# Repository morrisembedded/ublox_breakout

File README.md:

# ublox_breakout
EAGLE CAD files - Created in EAGLE 7.7.0

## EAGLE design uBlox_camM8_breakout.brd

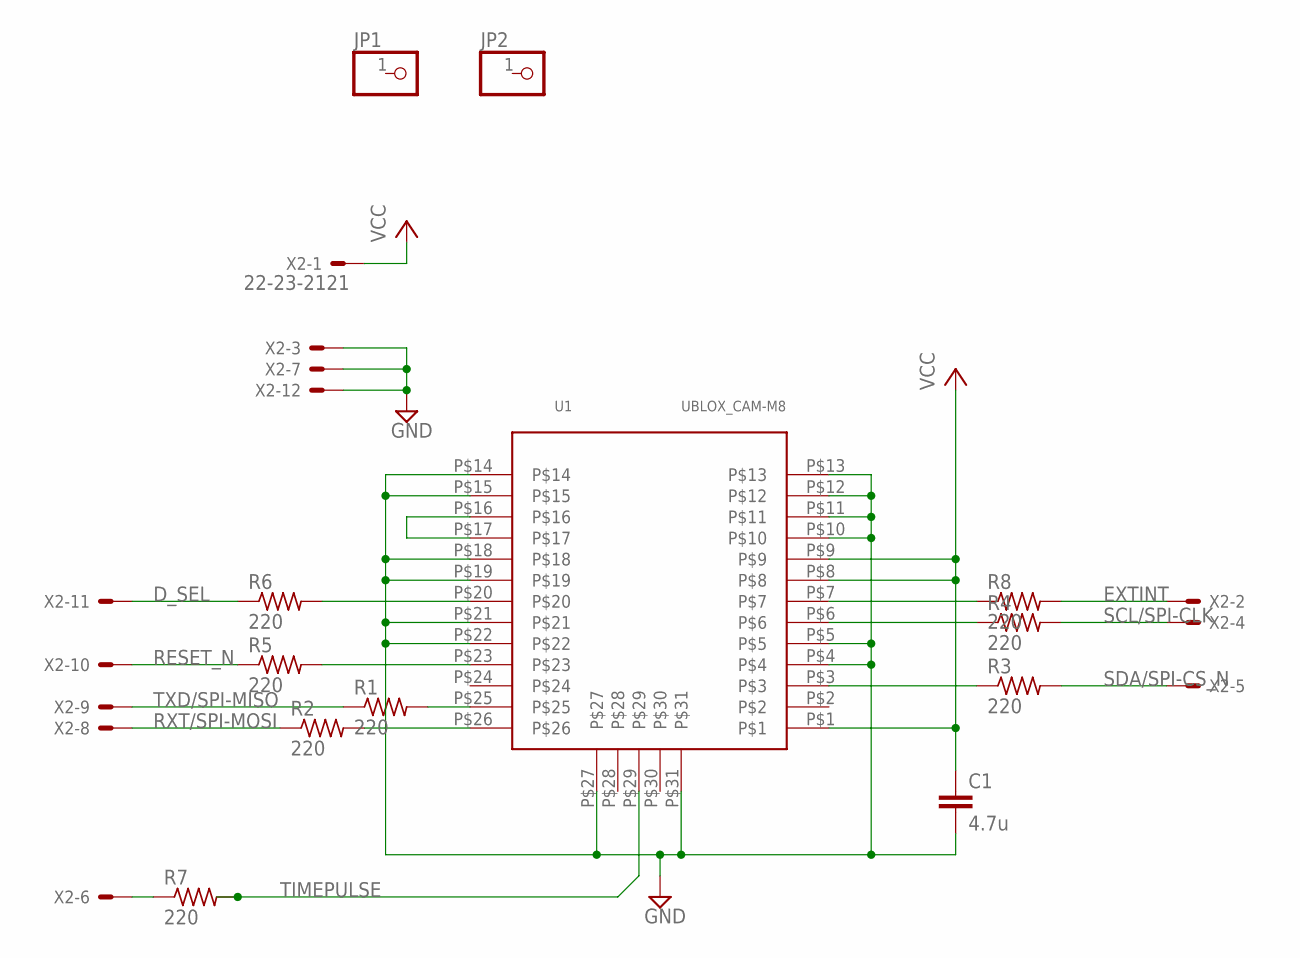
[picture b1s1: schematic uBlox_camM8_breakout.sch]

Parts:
C1: 4.7u; C0805
JP1, JP2: PINHD-1X1; 1X01
R1, R2, R3, R4, R5, R6, R7, R8: 220; R0402
U1: UBLOX_CAM-M8
X2: 22-23-2121

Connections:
D_SEL: R6.1, X2.11
EXTINT: R8.2, X2.2
GND: C1.2, U1.P$4, U1.P$5, U1.P$10, U1.P$11, U1.P$12, U1.P$13, U1.P$14, U1.P$15, U1.P$18, U1.P$19, U1.P$21, U1.P$22, U1.P$27, U1.P$31, X2.3, X2.7, X2.12
unnamed: R1.2, U1.P$25
unnamed: R2.2, U1.P$26
unnamed: U1.P$16, U1.P$17
unnamed: R3.1, U1.P$3
unnamed: R4.1, U1.P$6
unnamed: R8.1, U1.P$7
unnamed: R5.2, U1.P$23
unnamed: R6.2, U1.P$20
unnamed: R7.1, X2.6
RESET_N: R5.1, X2.10
RXT/SPI-MOSI: R2.1, X2.8
SCL/SPI-CLK: R4.2, X2.4
SDA/SPI-CS_N: R3.2, X2.5
TIMEPULSE: R7.2, U1.P$29
TXD/SPI-MISO: R1.1, X2.9
VCC: C1.1, U1.P$1, U1.P$8, U1.P$9, X2.1

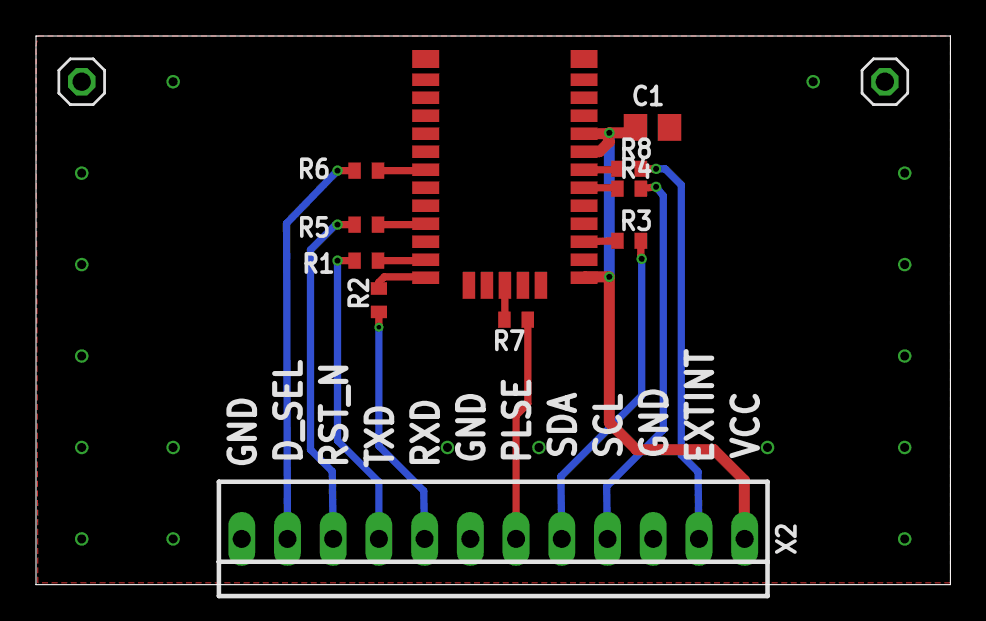
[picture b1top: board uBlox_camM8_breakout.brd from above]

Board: 2 copper layers, 50.8 x 30.5 mm, 13 parts (0 on the bottom side), 19 nets.
